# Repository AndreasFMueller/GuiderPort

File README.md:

GuiderPort

Most cameras for astrophotography have a guider port for autoguiding.
However, this is a really bad arrangment, because it requires an
additional cable between the telescope and the mount, adding an
additional force that could contribute to telescope flex. This
project offers the hardware and software for a standalone guider
port attached to a host computer via USB. This eliminates the need
for a guider port on the camera, and the guider port ist now directly
connected to the guiding computer.

The hardware uses an USB enable AVR microcontroller AT90USB162, but
an AT90USB82 is also sufficient. The schematics and board files in
KiCAD format are contained in the firmware directory. A suitable
case for the guider port hardware can be 3D-printed from the files
in the case subdirectory.

The firmware is based on the LUFA library. avr-gcc and avr-libc are
also needed to compile it. The Makefile contains targets to program
it using the avrispmk2 programmer and avrdude.

The client directory contains a libusb based client to test the
device.

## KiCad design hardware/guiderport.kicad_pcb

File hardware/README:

This directory contains the schematic and the board layout for the 
GuiderPort device created with KiCAD.

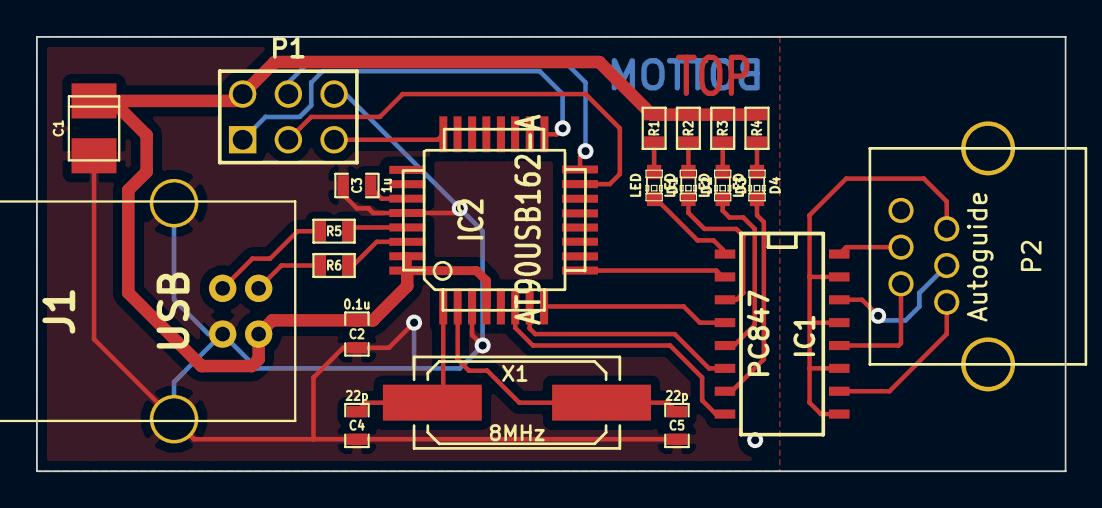
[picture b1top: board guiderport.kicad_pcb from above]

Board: 2 copper layers, 57.1 x 24.1 mm, 21 parts (0 on the bottom side), 30 nets.

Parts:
C1: 10u; c_tant_B
C2: 0.1u; SM0603_Capa
C3: 1u; SM0603_Capa
C4, C5: 22p; SM0603_Capa
D1, D2, D3, D4: LED; LED-0603
IC1: PC847; SO16N
IC2: AT90USB162-A; TQFP32
J1: USB; USB_B
P1: ISP; pin_array_3x2
P2: Autoguide; Guiderport
R1, R2, R3, R4: 390; SM0603
R5, R6: 22; SM0603
X1: 8MHz; Q_49U3HMS

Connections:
+5V: C1.1, C2.1, IC2.4, IC2.31, IC2.32, J1.1, P1.2, R1.1, R2.1, R3.1, R4.1
GND: C1.2, C2.2, C3.2, C4.2, C5.2, IC2.3, IC2.28, J1.4, J1.5, J1.6, P1.6
unnamed: C3.1, IC2.27
unnamed: IC2.29, R5.1
unnamed: J1.3, R5.2
unnamed: IC2.30, R6.1
unnamed: J1.2, R6.2
unnamed: IC1.8, IC2.6
unnamed: IC2.15, P1.3
unnamed: IC2.16, P1.4
unnamed: IC2.24, P1.5
unnamed: IC1.6, IC2.7
unnamed: IC1.4, IC2.8
unnamed: IC1.2, IC2.9
unnamed: C4.1, IC2.1, X1.1
unnamed: C5.1, IC2.2, X1.2
unnamed: IC2.17, P1.1
unnamed: D2.2, IC1.3
unnamed: D4.1, R4.2
unnamed: D4.2, IC1.7
unnamed: IC1.9, IC1.11, IC1.13, IC1.15, P2.2
unnamed: IC1.10, P2.6
unnamed: D3.2, IC1.5
unnamed: IC1.14, P2.4
unnamed: D1.2, IC1.1
unnamed: IC1.16, P2.3
unnamed: D1.1, R1.2
unnamed: D2.1, R2.2
unnamed: D3.1, R3.2
unnamed: IC1.12, P2.5

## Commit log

2015-06-07 initial release
2015-06-07 changes for release
2015-06-07 improve portability: old libusbs are somewhat difficient
2015-06-07 fix portability issues
2015-06-07 documentation
2015-06-07 add image
2015-06-07 add GET command
2015-06-07 complete documentation
2015-06-07 add get command to usage
2015-06-07 add LED holes to case
2015-06-08 add repeat/sleep options for long duration tests
2015-06-08 improve gaps
2015-06-09 add README for hardware directory
2015-06-09 fix descriptor
2015-06-09 fix descriptor (again)
2015-06-09 fix serial
2016-02-10 fix typo
2016-02-11 add serial command to firmware and client
2016-02-11 long options, help command
2018-05-03 address at90usb162 issues
2018-05-11 add missing serial.h
2018-05-11 add missing serial.c
2018-05-11 changes for tests with Dean
2018-05-11 client changes
2018-09-20 make serial 7 chars long
2019-09-06 add automatic firmware build date string
